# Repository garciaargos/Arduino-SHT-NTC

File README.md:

# Arduino-SHT-NTC
Read-out of SHT and NTC sensors with Arduino and ROOT

## Introduction

The Arduino firmware has only been tested with Arduino Uno. In principle it's possible to adapt it for other boards.

The SHT1x library can be obtained from the [Arduino Playground - Sensirion](http://playground.arduino.cc/Code/Sensirion).

You probably don't need the shield, but it might be handy. Feel free to use the design to build your own.

The dumped data is the read-out temperature and humidity for SHTs, but the resistor values for NTCs. This way the software communicating with the Arduino can take care of converting the resistance value to temperature, depending on the NTC used.

## Commands for the read-out configuration

- "READ": tells the Arduino to send the current read-out data. Works in non free-run mode.
- "SETMODE[0|1]": mode 0 makes the Arduino wait for the READ command to send data, mode 1 sends data every wait_time milliseconds. Mode 0 is the default.
- "SETDELAYn": sets the wait_time to n seconds.
- "SETMASKssssnnnnnn": sets the read-out mask, enabling first each of the 4 SHTs (s) and then each of the 6 NTCs (n). Enable with 1, disable with 0. Default mask is 1000111111. Only the first SHT is enabled.
- "SETRn,R": sets the resistor in series with NTC n (0-5) to value R in Ohms.

## Running the ROOT software

The only requirement is to download [ROOT](http://root.cern.ch). I've been using version 5.34.

If running on Windows, you might have to adjust some things, I've only tested under Linux. The port can be specified in the function arguments:

> root -x grTHlog_threads.cpp+(port_path, logfilename)

Note: when entering the arguments from the command line, escape the quotation marks as '\"':

> root -x grTHlog_threads.cpp+(\"/dev/ttyACM0\")

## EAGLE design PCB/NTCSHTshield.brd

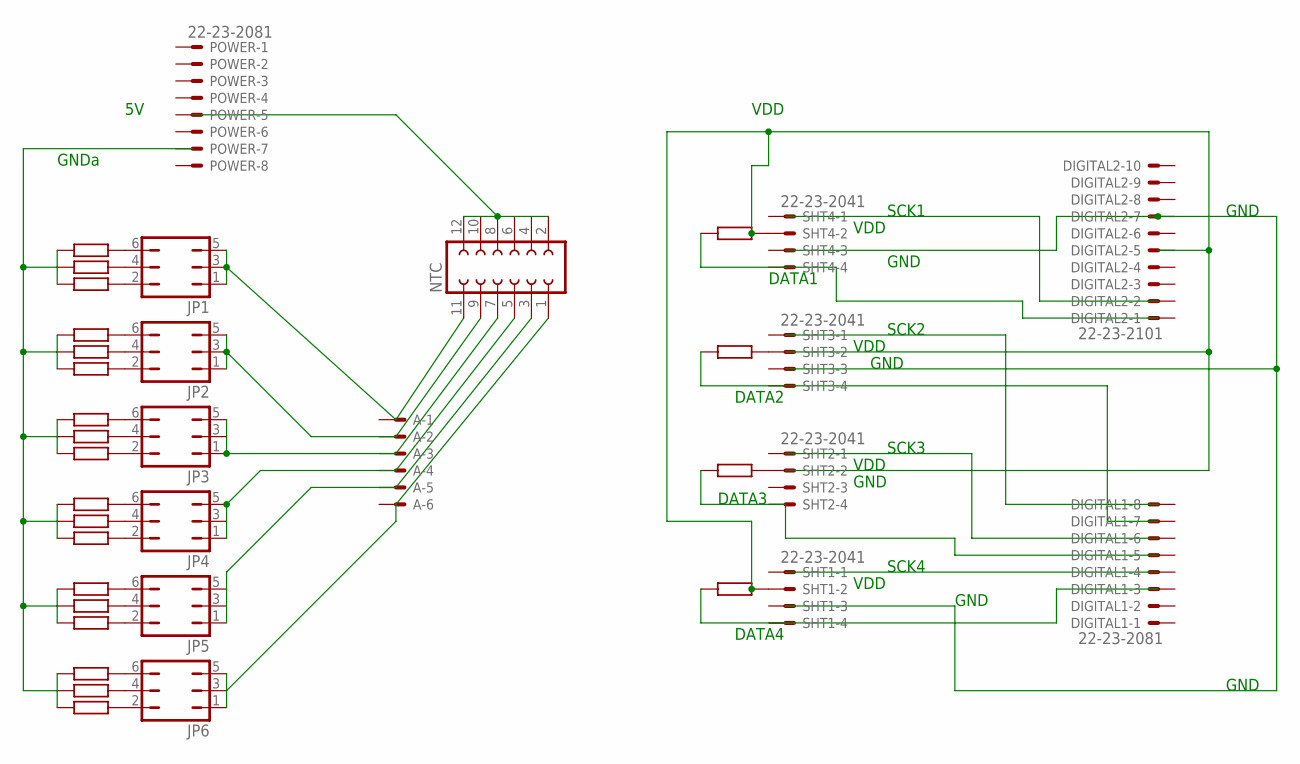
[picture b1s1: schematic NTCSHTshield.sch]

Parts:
A: 22-23-2061
DIGITAL1: 22-23-2081
DIGITAL2: 22-23-2101
JP1, JP2, JP3, JP4, JP5, JP6: JP3Q
NTC: FE06-2
POWER: 22-23-2081
SHT1, SHT2, SHT3, SHT4: 22-23-2041

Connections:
unnamed: JP2.1, JP2.3, JP2.5, NTC.9
unnamed: JP4.1, JP4.3, JP4.5, NTC.5
unnamed: JP6.1, JP6.3, JP6.5, NTC.1
unnamed: NTC.2, NTC.4, NTC.6, NTC.8, NTC.10, NTC.12
unnamed: JP1.1, JP1.3, JP1.5, NTC.11
unnamed: JP3.1, JP3.3, JP3.5, NTC.7
unnamed: JP5.1, JP5.3, JP5.5, NTC.3

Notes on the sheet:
GND
GNDa
SCK1
SCK2
SCK3
SCK4
DATA1
DATA2
DATA3
DATA4
VDD

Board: 2 copper layers, 15 parts (0 on the bottom side), 7 nets, no tracks yet.

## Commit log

2016-07-07 First polished version
2016-07-07 modified: Arduino/NTC_SHT_readout/NTC_SHT_readout.ino modified: README.md modified: ROOT/grTHlog_threads.cpp
2016-07-13 modified: README.md
2016-07-18 modified: ROOT/grTHlog_threads.cpp
